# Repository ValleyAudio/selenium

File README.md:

### Selenium
A modern replacement lightmeter for the ageing selenium meters in the Zenit SLR film cameras

Copyright (c) 2020 by Dale Johnson

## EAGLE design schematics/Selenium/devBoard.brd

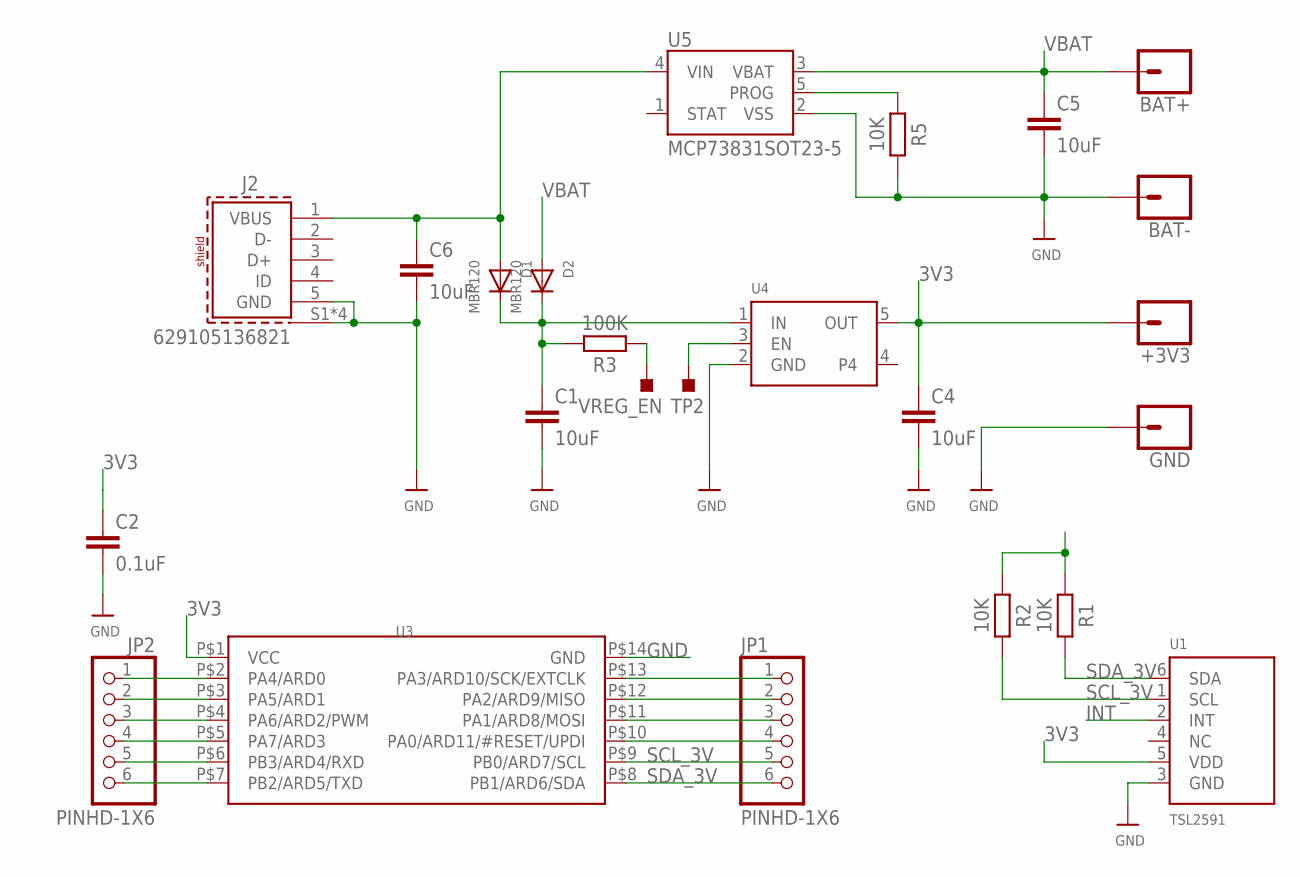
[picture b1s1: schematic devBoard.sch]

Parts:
+3V3: CONN_01; 1X01
BAT+: CONN_01; 1X01
BAT-: CONN_01; 1X01
C1, C4, C5, C6: 10uF; 0603
C2: 0.1uF; 0603
D1, D2: MBR120; SOD-123
GND: CONN_01; 1X01
J2: 629105136821
JP1, JP2: PINHD-1X6; 1X06
R1, R2, R5: 10K; RESC1608X60
R3: 100K; RESC1608X60
TP2: TESTPOINT_TPS-PAD-036; TESTPOINT_PAD-036
U1: TSL2591; DFN6_TAOS
U3: ATTINY1604; SOIC150
U4: VREG_SOT23-5; SOT23-5:1
U5: MCP73831SOT23-5; SOT95P280X110-5
VREG_EN: TESTPOINT_TPS-PAD-036; TESTPOINT_PAD-036

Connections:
3V3: +3V3.1, C2.1, C4.1, R1.1, R2.1, U1.5 (VDD), U3.P$1 (VCC), U4.5 (OUT)
GND: BAT-.1, C1.2, C2.2, C4.2, C5.2, C6.2, GND.1, J2.5 (GND), J2.S1 (SHIELD), J2.S2 (SHIELD), J2.S3 (SHIELD), J2.S4 (SHIELD), R5.2, U1.3 (GND), U3.P$14 (GND), U4.2 (GND), U5.2 (VSS)
INT: U1.2 (INT)
unnamed: C1.1, D1.C, D2.C, R3.2, U4.1 (IN)
unnamed: JP2.1, U3.P$2 (PA4/ARD0)
unnamed: JP2.2, U3.P$3 (PA5/ARD1)
unnamed: R5.1, U5.5 (PROG)
unnamed: JP2.3, U3.P$4 (PA6/ARD2/PWM)
unnamed: JP2.4, U3.P$5 (PA7/ARD3)
unnamed: JP2.5, U3.P$6 (PB3/ARD4/RXD)
unnamed: JP2.6, U3.P$7 (PB2/ARD5/TXD)
unnamed: JP1.4, U3.P$10 (PA0/ARD11/#RESET/UPDI)
unnamed: JP1.3, U3.P$11 (PA1/ARD8/MOSI)
unnamed: JP1.2, U3.P$12 (PA2/ARD9/MISO)
unnamed: JP1.1, U3.P$13 (PA3/ARD10/SCK/EXTCLK)
unnamed: R3.1, VREG_EN.1
unnamed: TP2.1, U4.3 (EN)
SCL_3V: JP1.5, R2.2, U1.1 (SCL), U3.P$9 (PB0/ARD7/SCL)
SDA_3V: JP1.6, R1.2, U1.6 (SDA), U3.P$8 (PB1/ARD6/SDA)
VBAT: BAT+.1, C5.1, D2.A, U5.3 (VBAT)
VBUS: C6.1, D1.A, J2.1 (VBUS), U5.4 (VIN)

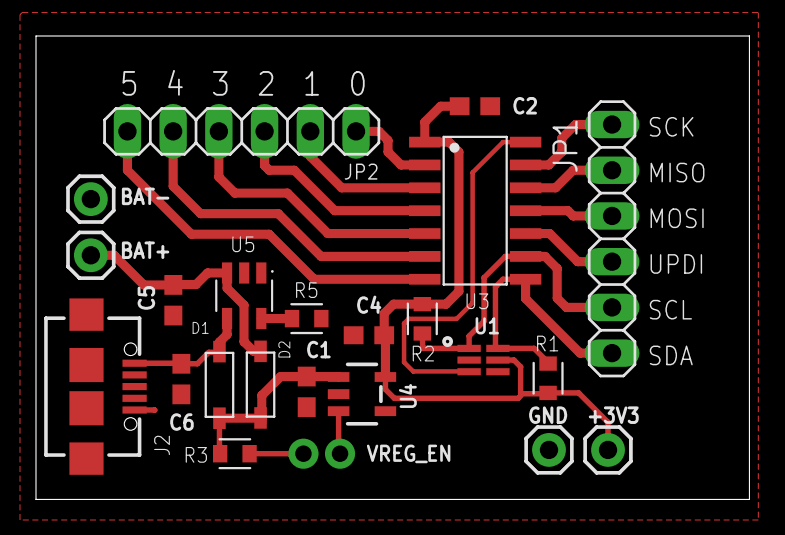
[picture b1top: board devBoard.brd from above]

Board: 2 copper layers, 39.6 x 25.7 mm, 24 parts (0 on the bottom side), 20 nets.

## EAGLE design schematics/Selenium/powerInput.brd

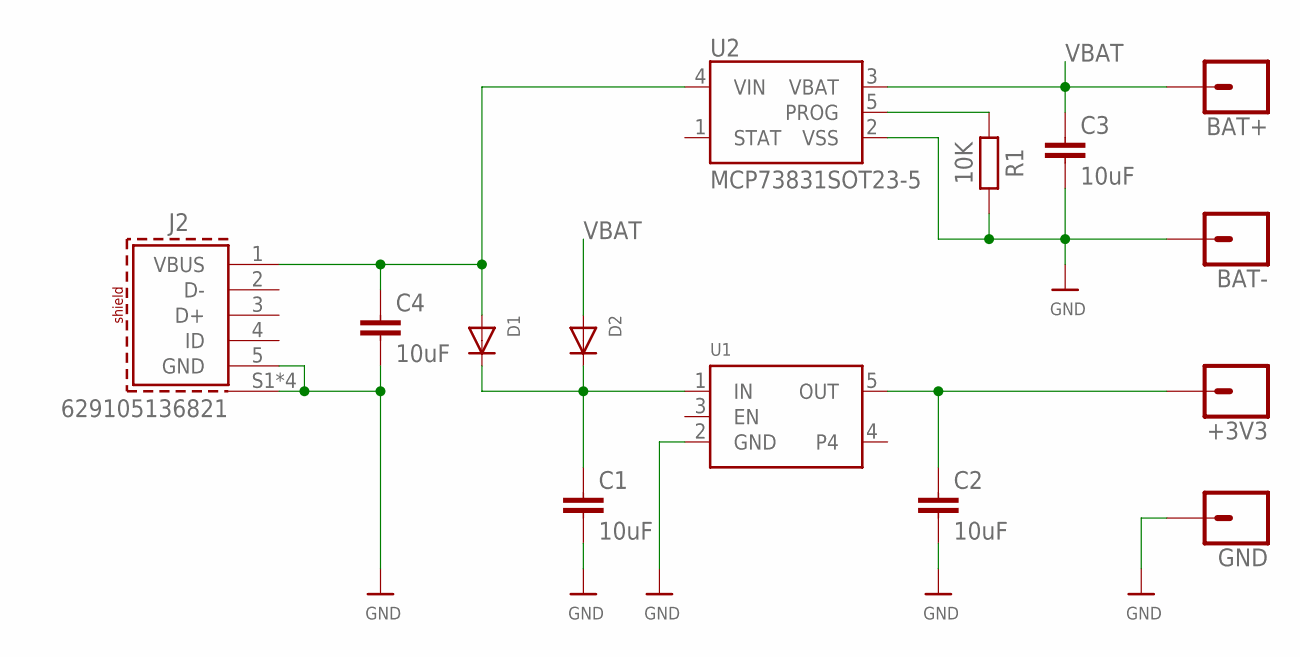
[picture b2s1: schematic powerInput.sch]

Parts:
+3V3: CONN_01; 1X01
BAT+: CONN_01; 1X01
BAT-: CONN_01; 1X01
C1, C2, C3, C4: 10uF; 0603
D1, D2: DIODESOD-123; SOD-123
GND: CONN_01; 1X01
J2: 629105136821
R1: 10K; RESC1608X60
U1: VREG_SOT23-5; SOT23-5:1
U2: MCP73831SOT23-5; SOT95P280X110-5

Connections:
GND: BAT-.1, C1.2, C2.2, C3.2, C4.2, GND.1, J2.5 (GND), J2.S1 (SHIELD), J2.S2 (SHIELD), J2.S3 (SHIELD), J2.S4 (SHIELD), R1.2, U1.2 (GND), U2.2 (VSS)
unnamed: C1.1, D1.C, D2.C, U1.1 (IN)
unnamed: R1.1, U2.5 (PROG)
OUT: +3V3.1, C2.1, U1.5 (OUT)
VBAT: BAT+.1, C3.1, D2.A, U2.3 (VBAT)
VBUS: C4.1, D1.A, J2.1 (VBUS), U2.4 (VIN)

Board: 2 copper layers, 14 parts (0 on the bottom side), 6 nets, no tracks yet.

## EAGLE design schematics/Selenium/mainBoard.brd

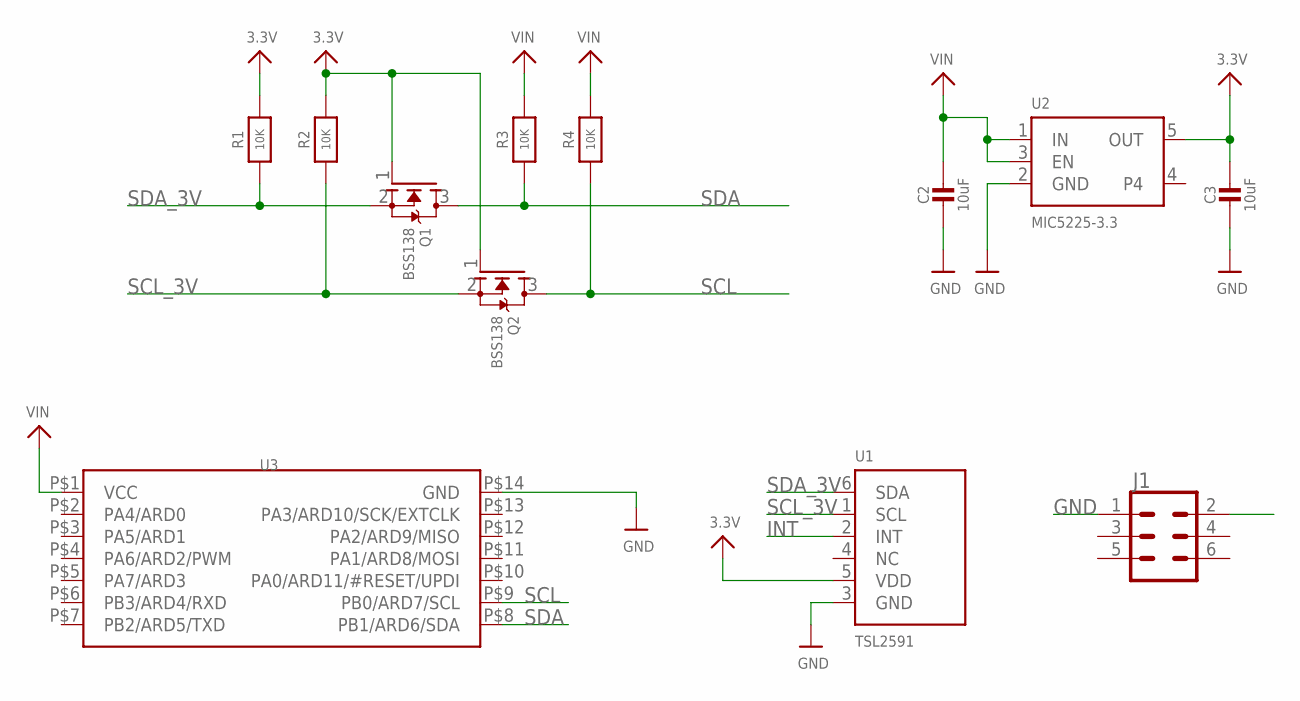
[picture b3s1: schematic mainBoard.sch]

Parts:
C2, C3: 10uF; 0805-NO
J1: CONN_03X22X3_SILK_MALE_PTH; 2X3
Q1, Q2: BSS138; SOT23-WIDE
R1, R2, R3, R4: 10K; 0805-NO
U1: TSL2591; DFN6_TAOS
U2: MIC5225-3.3; SOT23-5
U3: ATTINY1604; SOIC150

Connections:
3.3V: C3.1, Q1.1 (G), Q2.1 (G), R1.2, R2.2, U1.5 (VDD), U2.5 (OUT)
GND: C2.2, C3.2, J1.1, U1.3 (GND), U2.2 (GND), U3.P$14 (GND)
INT: U1.2 (INT)
SCL: Q2.3 (D), R4.1, U3.P$9 (PB0/ARD7/SCL)
SCL_3V: Q2.2 (S), R2.1, U1.1 (SCL)
SDA: Q1.3 (D), R3.1, U3.P$8 (PB1/ARD6/SDA)
SDA_3V: Q1.2 (S), R1.1, U1.6 (SDA)
VIN: C2.1, J1.2, R3.2, R4.2, U2.1 (IN), U2.3 (EN), U3.P$1 (VCC)

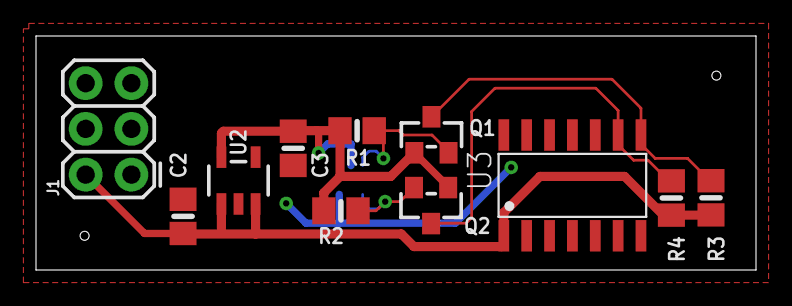
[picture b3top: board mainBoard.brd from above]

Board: 2 copper layers, 40.0 x 13.0 mm, 12 parts (1 on the bottom side), 7 nets.

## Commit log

2020-06-11 Init commit
2020-06-11 Alter copyright
2020-06-11 Move index to docs
2020-06-11 Remove index.html
2020-06-11 Test pages
2021-05-25 Update gitignore
2021-05-25 Add dev board EAGLE files
2021-05-25 Add libraries
2021-05-25 Add enable pin pads for regulator, tidy, then untrack backup files

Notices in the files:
parts and their libraries:
SparkFun-Connectors: Licensing: Creative Commons ShareAlike 4.0 International - https://creativecommons.org/licenses/by-sa/4.0
Wurth_Connectors_WR-USB: Copyright: Würth Elektronik
